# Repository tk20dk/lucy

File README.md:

# lucy
Low power DS18B20 sensor module

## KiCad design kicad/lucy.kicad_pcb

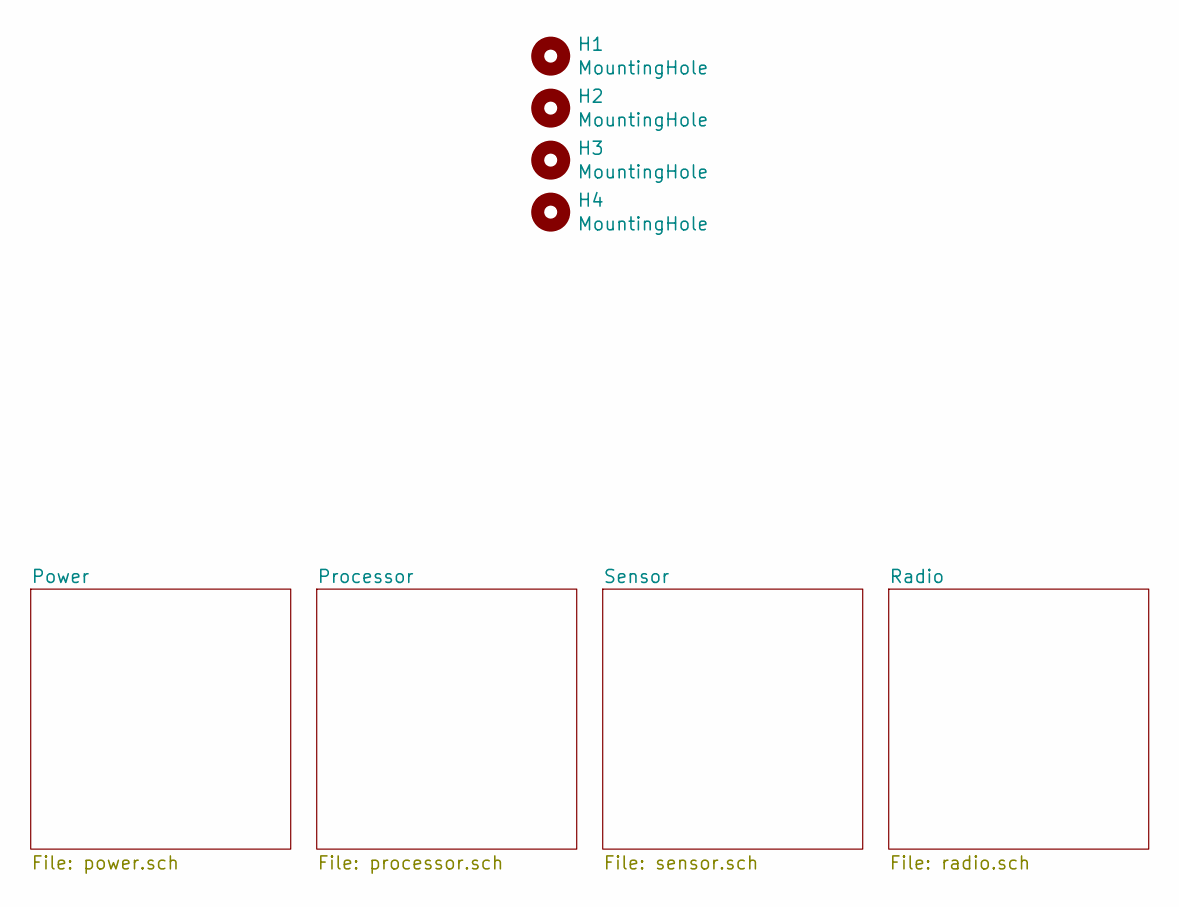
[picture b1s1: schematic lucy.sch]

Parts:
H1, H2, H3, H4: MountingHole; MountingHole_2.7mm

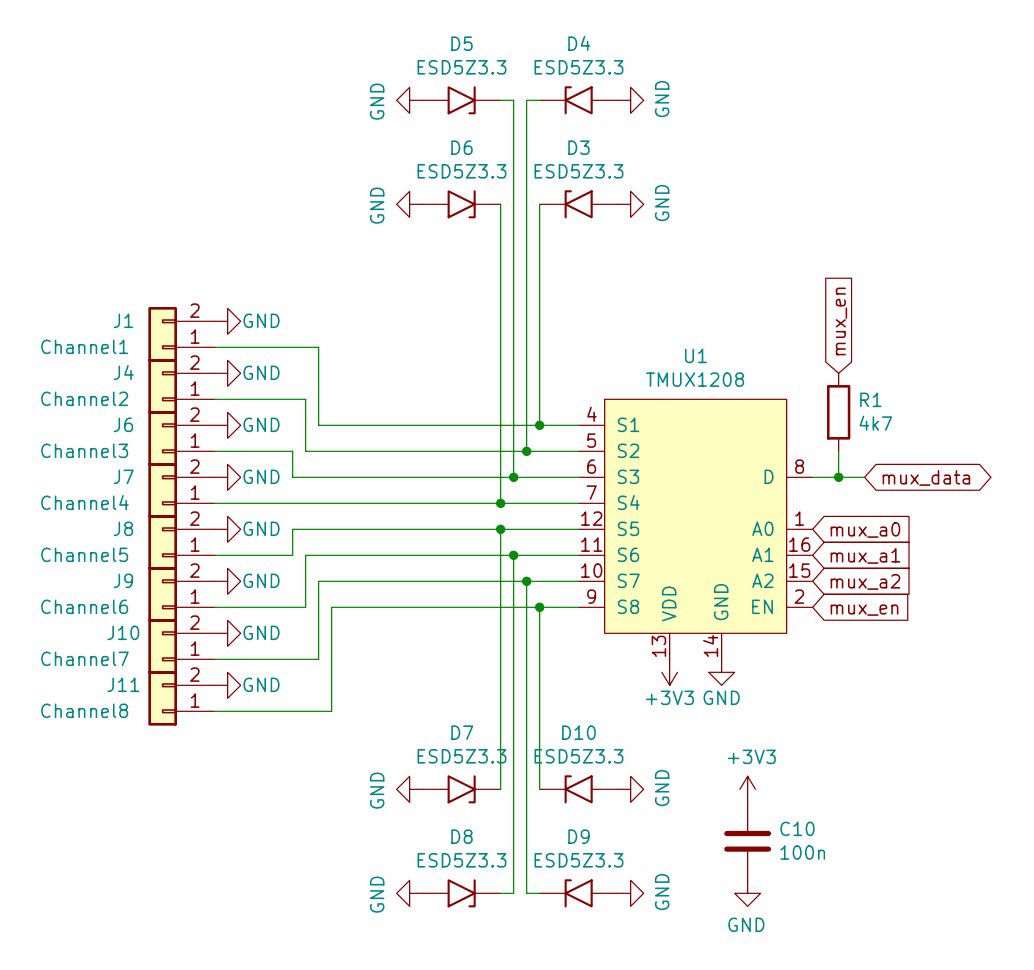
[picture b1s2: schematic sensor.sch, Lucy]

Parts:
C10: 100n; C_0603_1608Metric
D3, D4, D5, D6, D7, D8, D9, D10: ESD5Z3.3; D_SOD-523
J1: Channel1; Molex_PicoBlade_53048-0210_1x02_P1.25mm_Horizontal
J4: Channel2; Molex_PicoBlade_53048-0210_1x02_P1.25mm_Horizontal
J6: Channel3; Molex_PicoBlade_53048-0210_1x02_P1.25mm_Horizontal
J7: Channel4; Molex_PicoBlade_53048-0210_1x02_P1.25mm_Horizontal
J8: Channel5; Molex_PicoBlade_53048-0210_1x02_P1.25mm_Horizontal
J9: Channel6; Molex_PicoBlade_53048-0210_1x02_P1.25mm_Horizontal
J10: Channel7; Molex_PicoBlade_53048-0210_1x02_P1.25mm_Horizontal
J11: Channel8; Molex_PicoBlade_53048-0210_1x02_P1.25mm_Horizontal
R1: 4k7; R_0603_1608Metric
U1: TMUX1208; TSSOP-16_4.4x5mm_P0.65mm

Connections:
unnamed: D3.1 (A1), J1.1, U1.4 (S1)
unnamed: D4.1 (A1), J4.1, U1.5 (S2)
unnamed: D5.1 (A1), J6.1, U1.6 (S3)
unnamed: D6.1 (A1), J7.1, U1.7 (S4)
unnamed: D7.1 (A1), J8.1, U1.12 (S5)
unnamed: D8.1 (A1), J9.1, U1.11 (S6)
unnamed: D9.1 (A1), J10.1, U1.10 (S7)
unnamed: D10.1 (A1), J11.1, U1.9 (S8)
mux_a0: U1.1 (A0); also elsewhere on the board
mux_a1: U1.16 (A1); also elsewhere on the board
mux_a2: U1.15 (A2); also elsewhere on the board
mux_en: R1.1, U1.2 (EN); also elsewhere on the board

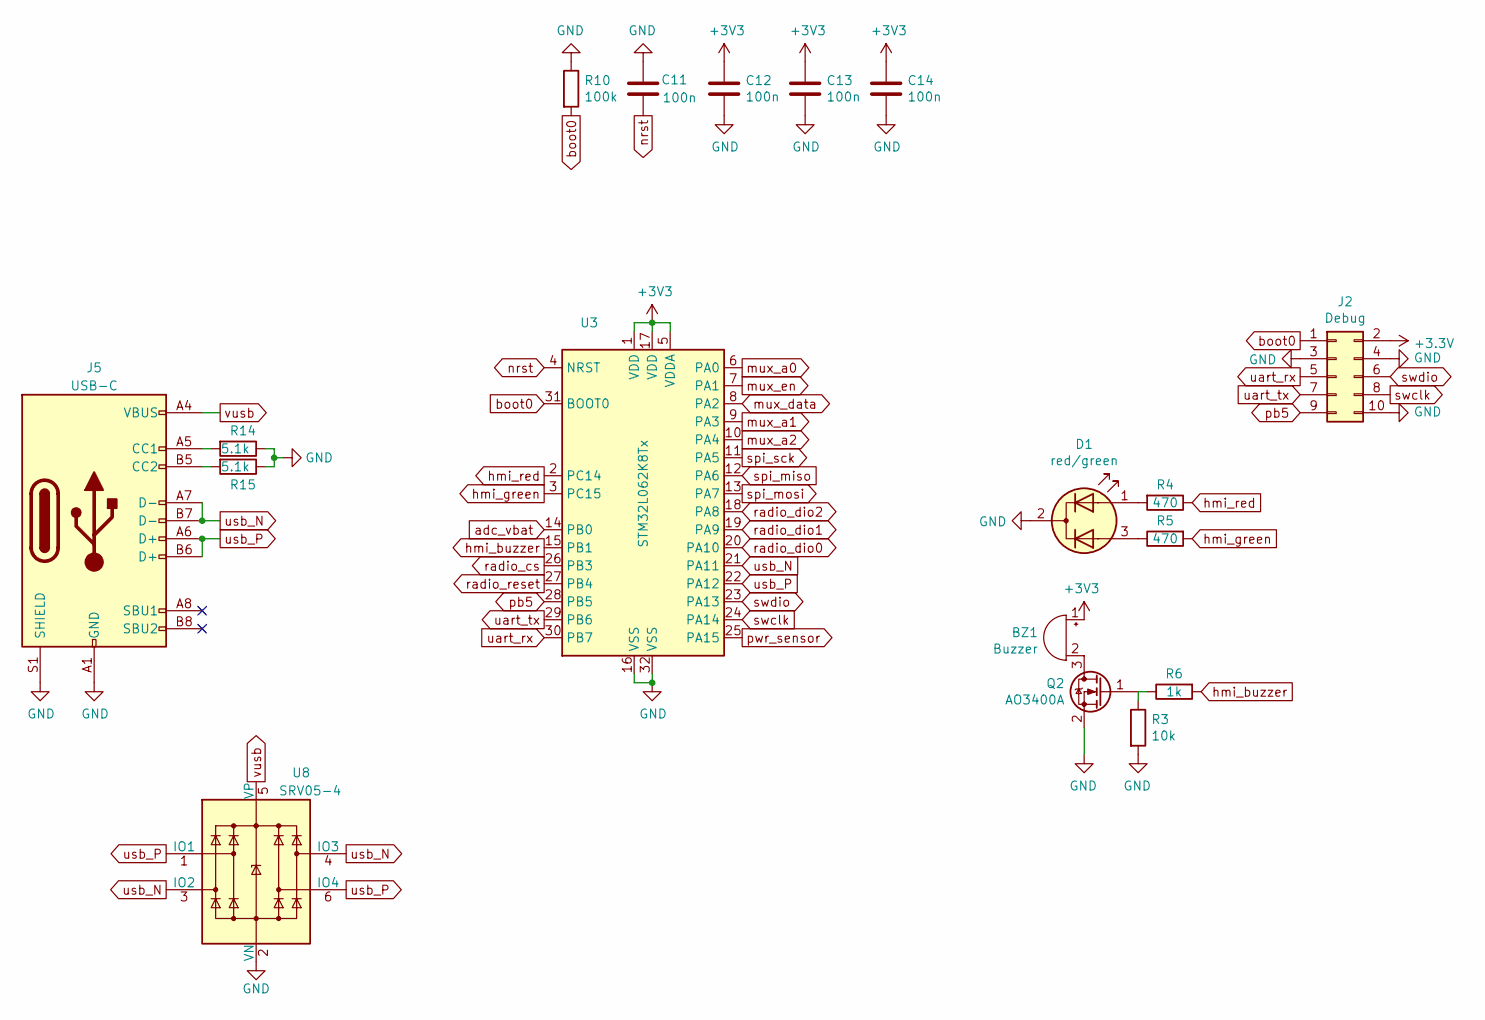
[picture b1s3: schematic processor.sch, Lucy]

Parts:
BZ1: Buzzer; Buzzer_12x9.5RM7.6
C11, C12, C13, C14: 100n; C_0603_1608Metric
D1: red/green; LED_D3.0mm-3
J2: Debug; PinHeader_2x05_P2.54mm_Vertical
J5: USB-C; USB_C_Receptacle_HRO_TYPE-C-31-M-12
Q2: AO3400A; SOT-23
R3: 10k; R_0603_1608Metric
R4, R5: 470; R_0603_1608Metric
R6: 1k; R_0603_1608Metric
R10: 100k; R_0603_1608Metric
R14, R15: 5.1k; R_0603_1608Metric
U3: STM32L062K8Tx; LQFP-32_7x7mm_P0.8mm
U8: SRV05-4; SOT-23-6

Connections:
unnamed: BZ1.2 (+), Q2.3 (D)
unnamed: D1.1 (A1), R4.2
unnamed: D1.3 (A2), R5.1
unnamed: J5.A5 (CC1), R14.2
unnamed: J5.B5 (CC2), R15.2
unnamed: Q2.1 (G), R3.1, R6.1
adc_vbat: U3.14 (PB0); also elsewhere on the board
boot0: J2.1, R10.2, U3.31 (BOOT0)
hmi_buzzer: R6.2, U3.15 (PB1)
hmi_green: R5.2, U3.3 (PC15)
hmi_red: R4.1, U3.2 (PC14)
mux_a0: U3.6 (PA0); also elsewhere on the board
mux_a1: U3.9 (PA3); also elsewhere on the board
mux_a2: U3.10 (PA4); also elsewhere on the board
mux_en: U3.7 (PA1); also elsewhere on the board
nrst: C11.1, U3.4 (NRST)
pwr_sensor: U3.25 (PA15); also elsewhere on the board
radio_cs: U3.26 (PB3); also elsewhere on the board
radio_dio0: U3.20 (PA10); also elsewhere on the board
radio_dio1: U3.19 (PA9); also elsewhere on the board
radio_dio2: U3.18 (PA8); also elsewhere on the board
radio_reset: U3.27 (PB4); also elsewhere on the board
spi_miso: U3.12 (PA6); also elsewhere on the board
spi_mosi: U3.13 (PA7); also elsewhere on the board
spi_sck: U3.11 (PA5); also elsewhere on the board
swclk: J2.8, U3.24 (PA14)
swdio: J2.6, U3.23 (PA13)
uart_rx: J2.5, U3.30 (PB7)
uart_tx: J2.7, U3.29 (PB6)
usb_N: J5.A7 (D-), J5.B7 (D-), U3.21 (PA11), U8.3 (IO2), U8.4 (IO3)
usb_P: J5.A6 (D+), J5.B6 (D+), U3.22 (PA12), U8.1 (IO1), U8.6 (IO4)
vusb: J5.A4 (VBUS), J5.A9 (VBUS), J5.B4 (VBUS), J5.B9 (VBUS), U8.5 (VP); also elsewhere on the board

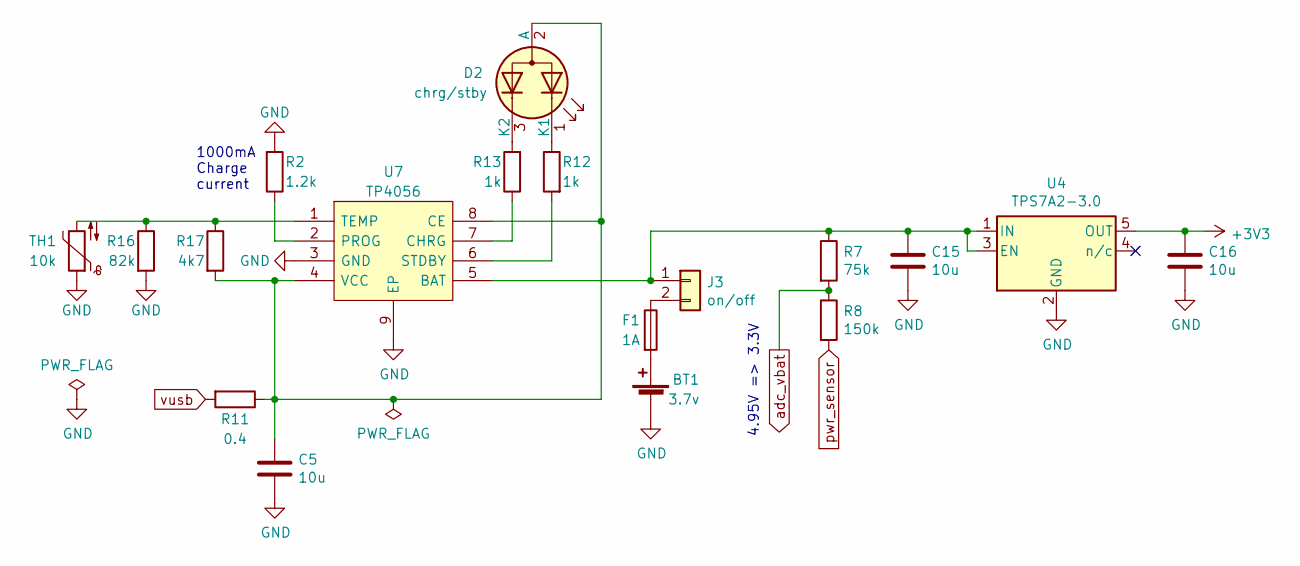
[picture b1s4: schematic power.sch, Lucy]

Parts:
BT1: 3.7v; 18650
C5: 10u; C_1206_3216Metric
C15, C16: 10u; C_0805_2012Metric
D2: chrg/stby; LED_D3.0mm-3
F1: 1A; Fuse_1206_3216Metric
J3: on/off; PinHeader_1x02_P2.54mm_Vertical
R2: 1.2k; R_0603_1608Metric
R7: 75k; R_0603_1608Metric
R8: 150k; R_0603_1608Metric
R11: 0.4; R_1206_3216Metric
R12, R13: 1k; R_0603_1608Metric
R16: 82k; R_0603_1608Metric
R17: 4k7; R_0603_1608Metric
TH1: 10k; NTC_th
U4: TPS7A2-3.0; SOT-23-5
U7: TP4056; SOIC127P600X175-9N; Manufacturer_Part_Number TP4056

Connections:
unnamed: BT1.1 (+), F1.2
unnamed: C5.1, D2.2 (A), R11.1, R17.2, U7.4 (VCC), U7.8 (CE)
unnamed: C15.1, J3.1, R7.1, U4.1 (IN), U4.3 (EN), U7.5 (BAT)
unnamed: D2.1 (K1), R12.1
unnamed: D2.3 (K2), R13.2
unnamed: F1.1, J3.2
unnamed: R2.1, U7.2 (PROG)
unnamed: R12.2, U7.6 (STDBY)
unnamed: R13.1, U7.7 (CHRG)
unnamed: R16.1, R17.1, TH1.2, U7.1 (TEMP)
adc_vbat: R7.2, R8.1; also elsewhere on the board
pwr_sensor: R8.2; also elsewhere on the board
vusb: R11.2; also elsewhere on the board

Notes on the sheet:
4.95V => 3.3V
1000mA Charge current

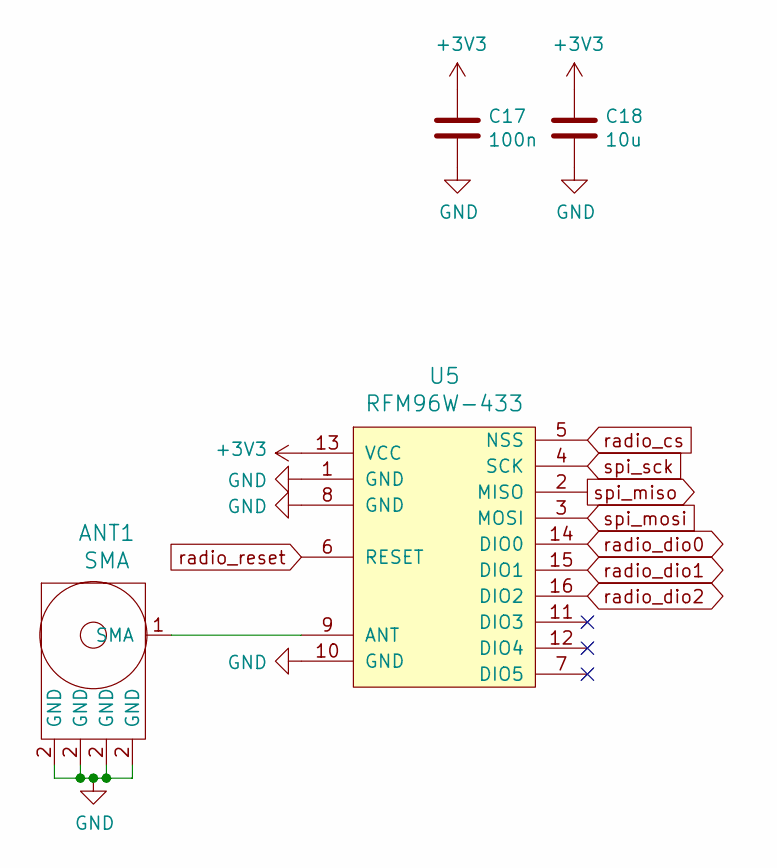
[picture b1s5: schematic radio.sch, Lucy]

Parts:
ANT1: SMA; CON-SMA
C17: 100n; C_0603_1608Metric
C18: 10u; C_0805_2012Metric
U5: RFM96W-433; RFM95W

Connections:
unnamed: ANT1.1 (SMA), U5.9 (ANT)
radio_cs: U5.5 (NSS); also elsewhere on the board
radio_dio0: U5.14 (DIO0); also elsewhere on the board
radio_dio1: U5.15 (DIO1); also elsewhere on the board
radio_dio2: U5.16 (DIO2); also elsewhere on the board
radio_reset: U5.6 (RESET); also elsewhere on the board
spi_miso: U5.2 (MISO); also elsewhere on the board
spi_mosi: U5.3 (MOSI); also elsewhere on the board
spi_sck: U5.4 (SCK); also elsewhere on the board

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
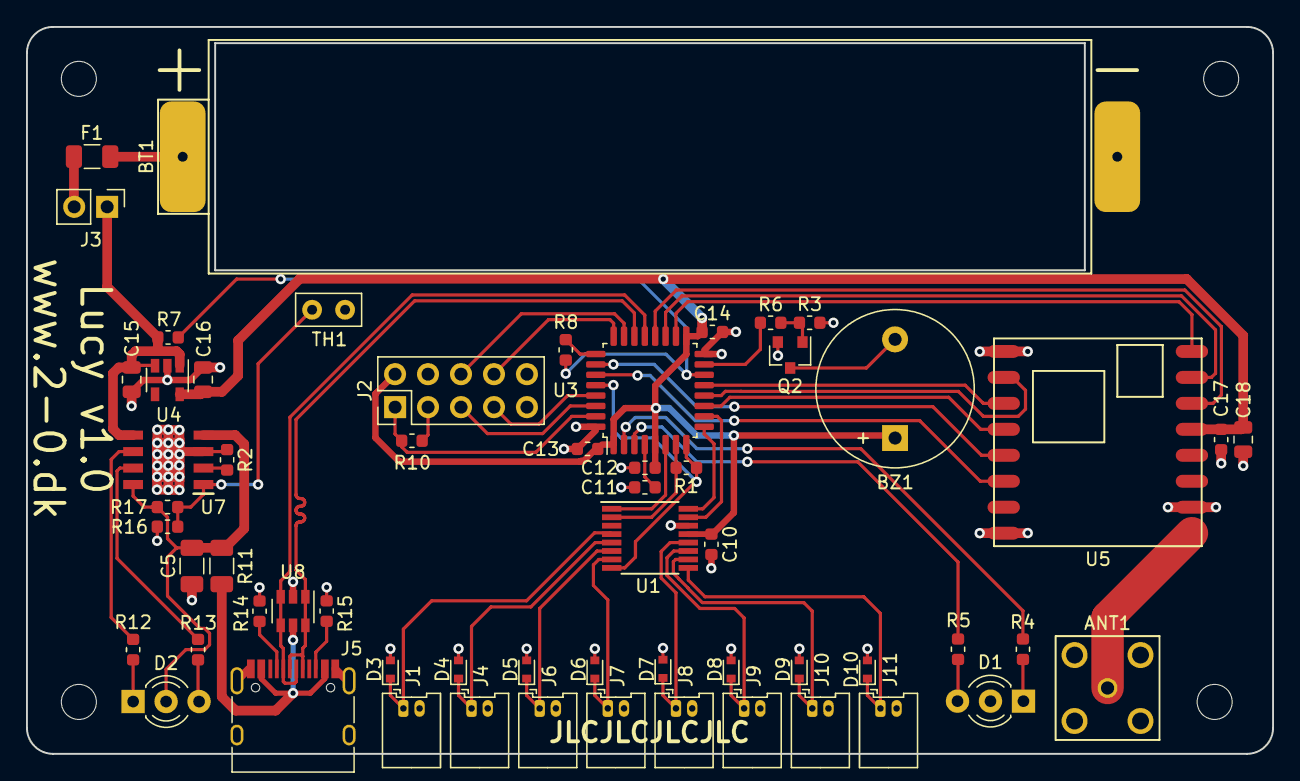
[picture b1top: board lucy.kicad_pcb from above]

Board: 2 copper layers, 96.0 x 56.0 mm, 63 parts (0 on the bottom side), 54 nets.

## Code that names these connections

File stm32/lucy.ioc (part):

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Mcu.Name=STM32L011K(3-4)Tx
Mcu.Package=LQFP32
Mcu.UserName=STM32L011K4Tx
PA0-CK_IN.GPIOParameters=GPIO_Label
PA0-CK_IN.GPIO_Label=MUX_A0
PA0-CK_IN.Signal=GPIO_Output
PA1.GPIOParameters=GPIO_Label
PA1.GPIO_Label=MUX_EN
PA1.Signal=GPIO_Output
PA10.GPIOParameters=GPIO_Label
PA10.GPIO_Label=RADIO_DIO0
PA10.Signal=GPXTI10
PA13.Mode=Serial_Wire
PA13.Signal=SYS_SWDIO
PA14.Mode=Serial_Wire
PA14.Signal=SYS_SWCLK
PA15.GPIOParameters=PinState,GPIO_Label
PA15.GPIO_Label=PWR_SENSOR
PA15.PinState=GPIO_PIN_RESET
PA15.Signal=GPIO_Output
PA2.GPIOParameters=GPIO_Label
PA2.GPIO_Label=MUX_DATA
PA2.Mode=Half_duplex(single_wire_mode)
PA2.Signal=USART2_TX
PA3.GPIOParameters=GPIO_Label
PA3.GPIO_Label=MUX_A1
PA3.Signal=GPIO_Output
PA4.GPIOParameters=GPIO_Label
PA4.GPIO_Label=MUX_A2
PA4.Signal=GPIO_Output
PA5.GPIOParameters=GPIO_Speed
PA5.GPIO_Speed=GPIO_SPEED_FREQ_HIGH
PA5.Mode=Full_Duplex_Master
PA5.Signal=SPI1_SCK
PA6.GPIOParameters=GPIO_Speed,GPIO_PuPd
PA6.GPIO_PuPd=GPIO_PULLUP
PA6.GPIO_Speed=GPIO_SPEED_FREQ_HIGH
PA6.Mode=Full_Duplex_Master
PA6.Signal=SPI1_MISO
PA7.GPIOParameters=GPIO_Speed
PA7.GPIO_Speed=GPIO_SPEED_FREQ_HIGH
PA7.Mode=Full_Duplex_Master
PA7.Signal=SPI1_MOSI
PA8.GPIOParameters=GPIO_Label
PA8.GPIO_Label=RADIO_DIO2
PA8.Signal=GPXTI8
PA9.GPIOParameters=GPIO_Label
PA9.GPIO_Label=RADIO_DIO1
PA9.Signal=GPXTI9
PB0.GPIOParameters=GPIO_Label
PB0.GPIO_Label=ADC_VBAT
PB0.Mode=IN8
PB0.Signal=ADC_IN8
PB1.GPIOParameters=GPIO_Label
PB1.GPIO_Label=HMI_BUZZER
PB1.Signal=GPIO_Output
PB3.GPIOParameters=GPIO_Label
PB3.GPIO_Label=RADIO_CS
PB3.Signal=GPIO_Output
PB4.GPIOParameters=GPIO_Label
PB4.GPIO_Label=RADIO_RESET
PB4.Signal=GPIO_Output
PB5.GPIOParameters=GPIO_Label
PB5.GPIO_Label=HMI_PB5
PB5.Signal=GPIO_Output
PB6.GPIOParameters=GPIO_Speed
PB6.GPIO_Speed=GPIO_SPEED_FREQ_LOW
PB6.Mode=Asynchronous
PB6.Signal=LPUART1_TX
PB7.GPIOParameters=GPIO_Speed,GPIO_PuPd
PB7.GPIO_PuPd=GPIO_PULLUP
PB7.GPIO_Speed=GPIO_SPEED_FREQ_LOW
PB7.Mode=Asynchronous
PB7.Signal=LPUART1_RX
PC14-OSC32_IN.GPIOParameters=GPIO_Label
PC14-OSC32_IN.GPIO_Label=HMI_RED
PC14-OSC32_IN.Signal=GPIO_Output
PC15-OSC32_OUT.GPIOParameters=GPIO_Label
PC15-OSC32_OUT.GPIO_Label=HMI_GREEN
PC15-OSC32_OUT.Signal=GPIO_Output
RCC.HSE_VALUE=8000000
RCC.SYSCLKFreq_VALUE=2097000
board=custom

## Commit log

2020-11-19 created initial kicad and stm32 projects
2020-11-23 lucy_v1.0
